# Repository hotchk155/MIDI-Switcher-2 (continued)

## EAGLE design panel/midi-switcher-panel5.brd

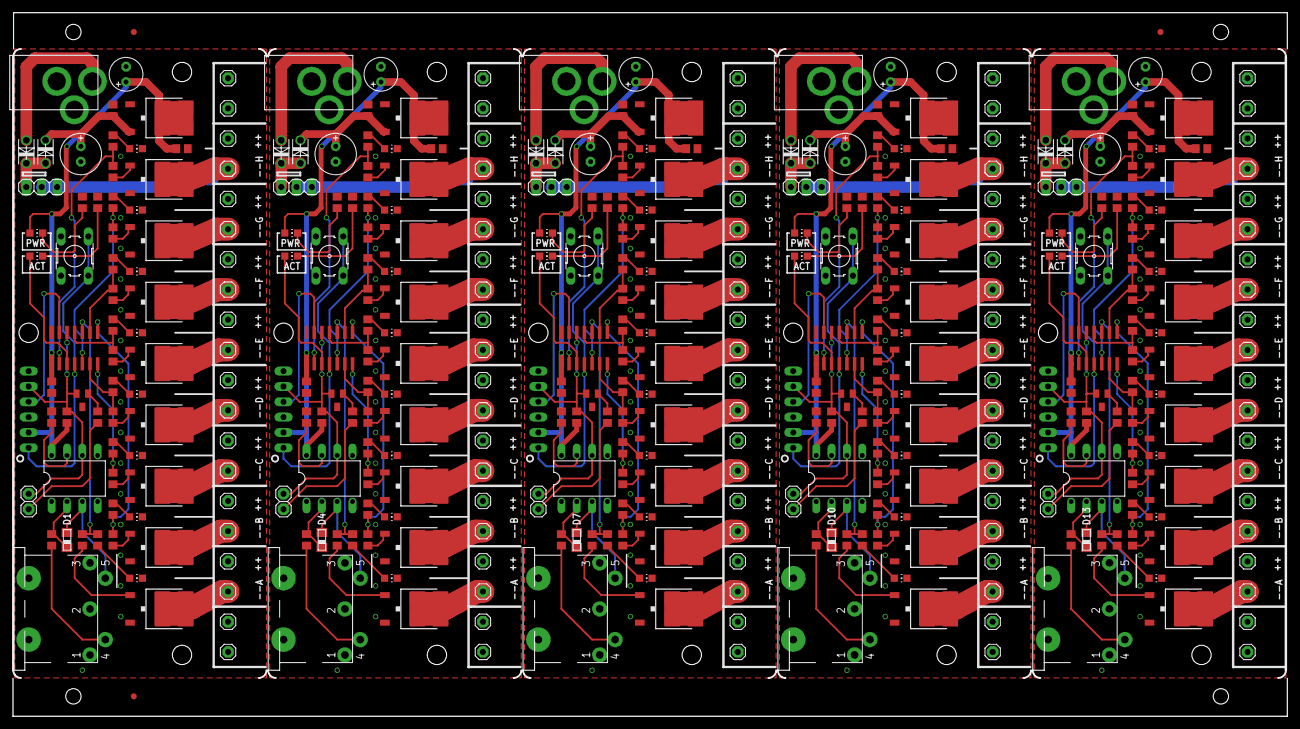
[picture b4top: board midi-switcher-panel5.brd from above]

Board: 2 copper layers, 210.8 x 116.3 mm, 398 parts (0 on the bottom side), 250 nets.

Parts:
C1, C2, C3, C6, C7, C8, C11, C12, C13, C16, C17, C18, C21, C22, C23: C0805
C4, C10, C15, C20, C25: E2,5-7
C5, C9, C14, C19, C24: E2,5-6
CHAIN_NEXT, CHAIN_NEXT1, CHAIN_NEXT2, CHAIN_NEXT3, CHAIN_NEXT4: 1X01
CHAIN_PREV, CHAIN_PREV1, CHAIN_PREV2, CHAIN_PREV3, CHAIN_PREV4: 1X01
D1, D4, D7, D10, D13: 0805DIODE
D2, D3, D5, D6, D8, D9, D11, D12, D14, D15: 1N4004; DO-VERT
E$1, E$2, E$3: FIDUCIAL_1MM
IC1, IC5, IC8, IC11, IC14: 6N138; DIL08
IC2, IC4, IC7, IC10, IC13: PIC16F1825SO14; SO14
IC3, IC6, IC9, IC12, IC15: LD1086; DPACK
ICSP, ICSP1, ICSP2, ICSP3, ICSP4: 1X06_OVAL
JP1, JP2, JP3, JP4, JP5: 1X03
L1, L2, L3, L4, L5, L6, L7, L8, L9, L10, L11, L12, L13, L14, L15, L16, L17, L18, L19, L20, L21, L22, L23, L24, L25, L26, L27, L28, L29, L30, L31, L32, L33, L34, L35, L36, L37, L38, L39, L40, L41, L42, L43, L44, L45, L46, L47, L48, L49, L50: CHIP-LED0805
MIDI_IN, MIDI_IN1, MIDI_IN2, MIDI_IN3, MIDI_IN4: DIN5PIN"; TRUCONN90
MODE, MODE1, MODE2, MODE3, MODE4: B3F-10XX
OP1+, OP1+1, OP1+2, OP1+3, OP1+4, OP1-, OP1-1, OP1-2, OP1-3, OP1-4, OP2+, OP2+1, OP2+2, OP2+3, OP2+4, OP2-, OP2-1, OP2-2, OP2-3, OP2-4, OP3+, OP3+1, OP3+2, OP3+3, OP3+4, OP3-, OP3-1, OP3-2, OP3-3, OP3-4, OP4+, OP4+1, OP4+2, OP4+3, OP4+4, OP4-, OP4-1, OP4-2, OP4-3, OP4-4, OP5+, OP5+1, OP5+2, OP5+3, OP5+4, OP5-, OP5-1, OP5-2, OP5-3, OP5-4, OP6-, OP6-1, OP6-2, OP6-3, OP6-4, OP7+, OP7+1, OP7+2, OP7+3, OP7+4, OP7-, OP7-1, OP7-2, OP7-3, OP7-4, OP8+, OP8+1, OP8+2, OP8+3, OP8+4, OP8+5, OP8+6, OP8+7, OP8+8, OP8+9, OP8-, OP8-1, OP8-2, OP8-3, OP8-4: 1X01
POWER+1, POWER+2, POWER+3, POWER+4, POWER+5, POWER+6, POWER+7, POWER+8, POWER+9, POWER+10: 1X01
POWER-1, POWER-2, POWER-3, POWER-4, POWER-5, POWER-6, POWER-7, POWER-8, POWER-9, POWER-10: 1X01
Q1, Q2, Q3, Q4, Q5, Q6, Q7, Q8, Q10, Q11, Q12, Q13, Q14, Q15, Q16, Q17, Q19, Q20, Q21, Q22, Q23, Q24, Q25, Q26, Q28, Q29, Q30, Q31, Q32, Q33, Q34, Q35, Q37, Q38, Q39, Q40, Q41, Q42, Q43, Q44: MJD122GDPAK; DPACK
Q9, Q18, Q27, Q36, Q45: SOT23-BEC
R1, R2, R3, R4, R5, R6, R7, R8, R9, R10, R11, R12, R13, R14, R15, R16, R17, R18, R19, R20, R21, R22, R23, R24, R25, R26, R27, R28, R29, R30, R31, R32, R33, R34, R35, R36, R37, R38, R39, R40, R41, R42, R43, R44, R45, R46, R47, R48, R49, R50, R51, R52, R53, R54, R55, R56, R57, R58, R59, R60, R61, R62, R63, R64, R65, R66, R67, R68, R69, R70, R71, R72, R73, R74, R75, R76, R77, R78, R79, R80, R81, R82, R83, R84, R85, R86, R87, R88, R89, R90, R91, R92, R93, R94, R95, R96, R97, R98, R99, R100, R101, R102, R103, R104, R105, R106, R107, R108, R109, R110: R0805
U$1, U$2, U$3, U$4, U$5: 2.1MMJACKTHM; PJ-102A

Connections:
+5V: C1.2, C2.1, C5.+, IC1.8, IC2.1, IC3.2, ICSP.2, L2.A, R22.2
+5V1: C6.1, C7.2, C9.+, IC4.1, IC5.8, IC6.2, ICSP1.2, L19.A, R5.2
+5V2: C11.1, C12.2, C14.+, IC7.1, IC8.8, IC9.2, ICSP2.2, L29.A, R46.2
+5V3: C16.1, C17.2, C19.+, IC10.1, IC11.8, IC12.2, ICSP3.2, L39.A, R68.2
+5V4: C21.1, C22.2, C24.+, IC13.1, IC14.8, IC15.2, ICSP4.2, L49.A, R90.2
+12V: JP3.2, JP3.3, OP1+.1, OP2+.1, OP3+.1, OP4+.1, OP5+.1, OP7+.1, OP8+.1, OP8+1.1, POWER+1.1, POWER+2.1
+12V1: JP1.2, JP1.3, OP1+1.1, OP2+1.1, OP3+1.1, OP4+1.1, OP5+1.1, OP7+1.1, OP8+2.1, OP8+3.1, POWER+3.1, POWER+4.1
+12V2: JP2.2, JP2.3, OP1+2.1, OP2+2.1, OP3+2.1, OP4+2.1, OP5+2.1, OP7+2.1, OP8+4.1, OP8+5.1, POWER+5.1, POWER+6.1
+12V3: JP4.2, JP4.3, OP1+3.1, OP2+3.1, OP3+3.1, OP4+3.1, OP5+3.1, OP7+3.1, OP8+6.1, OP8+7.1, POWER+7.1, POWER+8.1
+12V4: JP5.2, JP5.3, OP1+4.1, OP2+4.1, OP3+4.1, OP4+4.1, OP5+4.1, OP7+4.1, OP8+8.1, OP8+9.1, POWER+9.1, POWER+10.1
ACT_LED: IC2.3, L1.A
ACT_LED1: IC4.3, L20.A
ACT_LED2: IC7.3, L30.A
ACT_LED3: IC10.3, L40.A
ACT_LED4: IC13.3, L50.A
GND: C1.1, C2.2, C3.1, C4.-, C5.-, IC1.5, IC2.14, IC3.1, ICSP.3, L3.C, L4.C, L5.C, L6.C, L7.C, L8.C, L9.C, L10.C, MODE.3, MODE.4, POWER-1.1, POWER-2.1, Q1.3, Q2.3, Q3.3, Q4.3, Q5.3, Q6.3, Q7.3, Q8.3, Q9.C, R21.1, R24.2, R25.2, U$1.RING
GND1: C6.2, C7.1, C8.1, C9.-, C10.-, IC4.14, IC5.5, IC6.1, ICSP1.3, L11.C, L12.C, L13.C, L14.C, L15.C, L16.C, L17.C, L18.C, MODE1.3, MODE1.4, POWER-3.1, POWER-4.1, Q10.3, Q11.3, Q12.3, Q13.3, Q14.3, Q15.3, Q16.3, Q17.3, Q18.C, R6.1, R42.2, R43.2, U$2.RING
GND2: C11.2, C12.1, C13.1, C14.-, C15.-, IC7.14, IC8.5, IC9.1, ICSP2.3, L21.C, L22.C, L23.C, L24.C, L25.C, L26.C, L27.C, L28.C, MODE2.3, MODE2.4, POWER-5.1, POWER-6.1, Q19.3, Q20.3, Q21.3, Q22.3, Q23.3, Q24.3, Q25.3, Q26.3, Q27.C, R47.1, R64.2, R65.2, U$3.RING
GND3: C16.2, C17.1, C18.1, C19.-, C20.-, IC10.14, IC11.5, IC12.1, ICSP3.3, L31.C, L32.C, L33.C, L34.C, L35.C, L36.C, L37.C, L38.C, MODE3.3, MODE3.4, POWER-7.1, POWER-8.1, Q28.3, Q29.3, Q30.3, Q31.3, Q32.3, Q33.3, Q34.3, Q35.3, Q36.C, R69.1, R86.2, R87.2, U$4.RING
GND4: C21.2, C22.1, C23.1, C24.-, C25.-, IC13.14, IC14.5, IC15.1, ICSP4.3, L41.C, L42.C, L43.C, L44.C, L45.C, L46.C, L47.C, L48.C, MODE4.3, MODE4.4, POWER-9.1, POWER-10.1, Q37.3, Q38.3, Q39.3, Q40.3, Q41.3, Q42.3, Q43.3, Q44.3, Q45.C, R91.1, R108.2, R109.2, U$5.RING
MIDI_IN: CHAIN_NEXT.1, IC1.6, IC2.12, ICSP.5, Q9.E, R22.1
MIDI_IN1: CHAIN_NEXT1.1, IC4.12, IC5.6, ICSP1.5, Q18.E, R5.1
MIDI_IN2: CHAIN_NEXT2.1, IC7.12, IC8.6, ICSP2.5, Q27.E, R46.1
MIDI_IN3: CHAIN_NEXT3.1, IC10.12, IC11.6, ICSP3.5, Q36.E, R68.1
MIDI_IN4: CHAIN_NEXT4.1, IC13.12, IC14.6, ICSP4.5, Q45.E, R90.1
unnamed: D1.C, IC1.3, MIDI_IN.5
unnamed: MIDI_IN.4, R1.2
unnamed: D1.A, IC1.2, R1.1
unnamed: IC1.7, R21.2
unnamed: L1.C, R25.1
unnamed: L10.A, R20.2
unnamed: L9.A, R18.2
unnamed: Q8.1, R19.1
unnamed: Q7.1, R17.1
unnamed: Q6.1, R15.1
unnamed: Q5.1, R13.1
unnamed: Q4.1, R11.1
unnamed: Q3.1, R9.1
unnamed: Q2.1, R7.1
unnamed: Q1.1, R2.1
unnamed: Q9.B, R23.2
unnamed: Q11.1, R27.1
unnamed: CHAIN_PREV.1, R23.1
unnamed: Q12.1, R28.1
unnamed: Q13.1, R29.1
unnamed: Q14.1, R30.1
unnamed: Q15.1, R31.1
unnamed: Q16.1, R32.1
unnamed: L8.A, R16.2
unnamed: OP1-.1, Q8.2
unnamed: OP2-.1, Q7.2
unnamed: OP3-.1, Q6.2
unnamed: L2.C, R24.1
unnamed: OP5-.1, Q4.2
unnamed: OP6-.1, Q3.2
unnamed: OP4-.1, Q5.2
unnamed: Q17.1, R33.1
unnamed: L7.A, R14.2
unnamed: L11.A, R34.2
unnamed: L6.A, R12.2
unnamed: L5.A, R10.2
unnamed: L4.A, R8.2
unnamed: L3.A, R3.2
unnamed: C3.2, C4.+, D3.C, IC3.3
unnamed: L12.A, R35.2
unnamed: L13.A, R36.2
unnamed: OP7-.1, Q2.2
unnamed: D2.A, U$1.TIP
unnamed: L14.A, R37.2
unnamed: L15.A, R38.2
unnamed: L16.A, R39.2
unnamed: OP8-.1, Q1.2
unnamed: L17.A, R40.2
unnamed: L18.A, R41.2
unnamed: C8.2, C10.+, D5.C, IC6.3
unnamed: IC2.13, ICSP.4
unnamed: OP1-1.1, Q10.2
unnamed: OP2-1.1, Q11.2
unnamed: D2.C, D3.A, JP3.1
unnamed: OP3-1.1, Q12.2
unnamed: OP5-1.1, Q14.2
unnamed: OP6-1.1, Q15.2
unnamed: OP4-1.1, Q13.2
unnamed: OP7-1.1, Q16.2
unnamed: OP8-1.1, Q17.2
unnamed: IC4.13, ICSP1.4
unnamed: D6.A, U$2.TIP
unnamed: D5.A, D6.C, JP1.1
unnamed: L19.C, R42.1
unnamed: L20.C, R43.1
unnamed: D4.C, IC5.3, MIDI_IN1.5
unnamed: MIDI_IN1.4, R4.2
unnamed: D4.A, IC5.2, R4.1
unnamed: IC5.7, R6.2
unnamed: Q18.B, R44.2
unnamed: CHAIN_PREV1.1, R44.1
unnamed: Q10.1, R26.1
unnamed: Q20.1, R49.1
unnamed: Q21.1, R50.1
unnamed: Q22.1, R51.1
unnamed: Q23.1, R52.1
unnamed: Q24.1, R53.1
unnamed: Q25.1, R54.1
unnamed: Q26.1, R55.1
unnamed: L21.A, R56.2
unnamed: L22.A, R57.2
unnamed: L23.A, R58.2
unnamed: L24.A, R59.2
unnamed: L25.A, R60.2
unnamed: L26.A, R61.2
unnamed: L27.A, R62.2
unnamed: L28.A, R63.2
unnamed: C13.2, C15.+, D8.C, IC9.3
unnamed: OP1-2.1, Q19.2
unnamed: OP2-2.1, Q20.2
unnamed: OP3-2.1, Q21.2
unnamed: OP5-2.1, Q23.2
unnamed: OP6-2.1, Q24.2
unnamed: OP4-2.1, Q22.2
unnamed: OP7-2.1, Q25.2
unnamed: OP8-2.1, Q26.2
unnamed: IC7.13, ICSP2.4
unnamed: D9.A, U$3.TIP
unnamed: D8.A, D9.C, JP2.1
unnamed: L29.C, R64.1
unnamed: L30.C, R65.1
unnamed: D7.C, IC8.3, MIDI_IN2.5
unnamed: MIDI_IN2.4, R45.2
unnamed: D7.A, IC8.2, R45.1
unnamed: IC8.7, R47.2
unnamed: Q27.B, R66.2
unnamed: CHAIN_PREV2.1, R66.1
unnamed: Q19.1, R48.1
unnamed: Q29.1, R71.1
unnamed: Q30.1, R72.1
unnamed: Q31.1, R73.1
unnamed: Q32.1, R74.1
unnamed: Q33.1, R75.1
unnamed: Q34.1, R76.1
unnamed: Q35.1, R77.1
unnamed: L31.A, R78.2
unnamed: L32.A, R79.2
unnamed: L33.A, R80.2
unnamed: L34.A, R81.2
unnamed: L35.A, R82.2
unnamed: L36.A, R83.2
unnamed: L37.A, R84.2
unnamed: L38.A, R85.2
unnamed: C18.2, C20.+, D11.C, IC12.3
unnamed: OP1-3.1, Q28.2
unnamed: OP2-3.1, Q29.2
unnamed: OP3-3.1, Q30.2
unnamed: OP5-3.1, Q32.2
unnamed: OP6-3.1, Q33.2
unnamed: OP4-3.1, Q31.2
unnamed: OP7-3.1, Q34.2
unnamed: OP8-3.1, Q35.2
unnamed: IC10.13, ICSP3.4
unnamed: D12.A, U$4.TIP
unnamed: D11.A, D12.C, JP4.1
unnamed: L39.C, R86.1
unnamed: L40.C, R87.1
unnamed: D10.C, IC11.3, MIDI_IN3.5
unnamed: MIDI_IN3.4, R67.2
unnamed: D10.A, IC11.2, R67.1
unnamed: IC11.7, R69.2
unnamed: Q36.B, R88.2
unnamed: CHAIN_PREV3.1, R88.1
unnamed: Q28.1, R70.1
unnamed: Q38.1, R93.1
unnamed: Q39.1, R94.1
unnamed: Q40.1, R95.1
unnamed: Q41.1, R96.1
unnamed: Q42.1, R97.1
unnamed: Q43.1, R98.1
unnamed: Q44.1, R99.1
unnamed: L41.A, R100.2
unnamed: L42.A, R101.2
unnamed: L43.A, R102.2
unnamed: L44.A, R103.2
unnamed: L45.A, R104.2
unnamed: L46.A, R105.2
unnamed: L47.A, R106.2
unnamed: L48.A, R107.2
unnamed: C23.2, C25.+, D14.C, IC15.3
unnamed: OP1-4.1, Q37.2
unnamed: OP2-4.1, Q38.2
unnamed: OP3-4.1, Q39.2
unnamed: OP5-4.1, Q41.2
unnamed: OP6-4.1, Q42.2
unnamed: OP4-4.1, Q40.2
unnamed: OP7-4.1, Q43.2
unnamed: OP8-4.1, Q44.2
unnamed: IC13.13, ICSP4.4
unnamed: D15.A, U$5.TIP
unnamed: D14.A, D15.C, JP5.1
unnamed: L49.C, R108.1
unnamed: L50.C, R109.1
unnamed: D13.C, IC14.3, MIDI_IN4.5
unnamed: MIDI_IN4.4, R89.2
unnamed: D13.A, IC14.2, R89.1
unnamed: IC14.7, R91.2
unnamed: Q45.B, R110.2
unnamed: CHAIN_PREV4.1, R110.1
unnamed: Q37.1, R92.1
OUT1: IC2.2, R19.2, R20.1
OUT2: IC2.5, R17.2, R18.1
OUT3: IC2.9, R15.2, R16.1
OUT4: IC2.11, R13.2, R14.1
OUT5: IC2.6, R11.2, R12.1
OUT6: IC2.7, R9.2, R10.1
OUT7: IC2.8, R7.2, R8.1
OUT8: IC2.10, R2.2, R3.1
OUT9: IC4.9, R28.2, R36.1
OUT10: IC4.11, R29.2, R37.1
OUT11: IC4.6, R30.2, R38.1
OUT12: IC4.7, R31.2, R39.1
OUT13: IC4.5, R27.2, R35.1
OUT14: IC4.2, R26.2, R34.1
OUT15: IC4.10, R33.2, R41.1
OUT16: IC4.8, R32.2, R40.1
OUT17: IC7.9, R50.2, R58.1
OUT18: IC7.11, R51.2, R59.1
OUT19: IC7.6, R52.2, R60.1
OUT20: IC7.7, R53.2, R61.1
OUT21: IC7.5, R49.2, R57.1
OUT22: IC7.2, R48.2, R56.1
OUT23: IC7.10, R55.2, R63.1
OUT24: IC7.8, R54.2, R62.1
OUT25: IC10.9, R72.2, R80.1
OUT26: IC10.11, R73.2, R81.1
OUT27: IC10.6, R74.2, R82.1
OUT28: IC10.7, R75.2, R83.1
OUT29: IC10.5, R71.2, R79.1
OUT30: IC10.2, R70.2, R78.1
OUT31: IC10.10, R77.2, R85.1
OUT32: IC10.8, R76.2, R84.1
OUT33: IC13.9, R94.2, R102.1
OUT34: IC13.11, R95.2, R103.1
OUT35: IC13.6, R96.2, R104.1
OUT36: IC13.7, R97.2, R105.1
OUT37: IC13.5, R93.2, R101.1
OUT38: IC13.2, R92.2, R100.1
OUT39: IC13.10, R99.2, R107.1
OUT40: IC13.8, R98.2, R106.1
SWITCH: IC2.4, ICSP.1, MODE.1, MODE.2
SWITCH1: IC4.4, ICSP1.1, MODE1.1, MODE1.2
SWITCH2: IC7.4, ICSP2.1, MODE2.1, MODE2.2
SWITCH3: IC10.4, ICSP3.1, MODE3.1, MODE3.2
SWITCH4: IC13.4, ICSP4.1, MODE4.1, MODE4.2

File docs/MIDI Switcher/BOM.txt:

C1                        100n
C2                        100n
C3                        100n
C4                        47u
C5                        47u
D1         0805DIODE      0805DIODE                 0805DIODE                                                                                             
D2         1N4004         1N4004                    DO-VERT      DIODE                                                                                    
D3         1N4004         1N4004                    DO-VERT      DIODE                                                                                    
IC1        6N138          6N138                     DIL08        MOTOROLA OPTO COUPLER                                                                    
IC2        PIC16F1825SO14 PIC16F1825SO14            SO14                                                                                                  
IC3        LD1086         LD1086                    DPACK                                                                                                 
L1                        LED0805
L2                        LED0805
L3                        LED0805
L4                        LED0805
L5                        LED0805
L6                        LED0805
L7                        LED0805
L8                        LED0805
L9                        LED0805
L10                       LED0805
MIDI_IN    DIN5PIN"       DIN5PIN"                  TRUCONN90    Female CONNECTOR                                                                         
MODE                      10-XX                     B3F-10XX     OMRON SWITCH                                                                             
Q1         				  MJD122
Q2         				  MJD122
Q3         				  MJD122
Q4         				  MJD122
Q5         				  MJD122
Q6         				  MJD122
Q7         MJD122GDPAK    MJD122         				  MJD122
Q8         				  MJD122
Q9                        MMBT3906
R1                        220
R2                        1K
R3                        1K
R7                        1K
R8                        1K
R9                        1K
R10                       1K
R11                       1K
R12                       1K
R13                       1K
R14                       1K
R15                       1K
R16                       1K
R17                       1K
R18                       1K
R19                       1K
R20                       1K
R21                       1K5
R22                       1K5
R23                       1K
R24                       1K
R25                       1K
U$1        2.1MMJACKTHM   2.1MMJACKTHM              PJ-102A      2.1mm x 5.5mm THM DC jack with internal switch. Digikey part #PJ-102A, 4UCON part #05537

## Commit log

2018-07-10 moved board to new project
2018-08-23 pcb updates rev2
2018-08-23 tidy up
2018-08-28 segment large pads/tidy up
2018-10-10 dsgfdf
2018-10-10 gdsfgd
2018-10-16 dfes
2018-10-18 dsfs
2018-10-18 update gitignore
2018-10-19 version 1?
2018-10-22 prep v1
2018-10-22 pgm renumbering
2018-10-22 pgm fix
2018-10-22 change to handling of pulse shape defaults
2018-10-22 fix to sustain
2018-10-22 VERSION 1 TESTED
2018-10-22 rev1.0 sysex
2018-11-29 support latching mode
2018-12-02 v1.1 - allow latching mode and special reset states
2019-02-25 REV3 board - increase ground plane isolation on bottom
2019-02-25 Revert "REV3 board - increase ground plane isolation on bottom"
    This reverts commit 9a92895ae1f12a77b62d7c6f56f5905224b33e44.
2019-02-25 REV3 - increase bottom copper pour clearance. Silk changes
2019-02-25 panelised
2019-03-11 change pin hole size
2019-05-01 Support inverted output mode
2019-05-01 Invert option configured as flags byte
2020-04-28 1.2 24apr20 support relay switcher
2020-05-01 bring in new relay switcher stuff
2020-05-01 relay stuff
2020-09-29 Update midi-switcher-panel5.brd
    fix silk screen issues with panel
2020-09-30 waaaa
2021-07-27 TRS switcher added
2021-07-27 dpdt added
2021-07-27 first layout dpdt
2021-12-11 ssr switcher v1
2022-12-19 catchup
2024-10-24 1.2A BETA support note ranges
2024-10-24 support note range
2024-10-24 latch function into UI
2024-10-25 fix config page
2025-04-29 rename midi switcher to midi switcher smt
2026-02-06 Rev 3B board (single) enlarge terminal pin holes
2026-02-26 first cut xc8 vscode
